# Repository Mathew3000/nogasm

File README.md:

# Warning
The pcb is not fully tested yet. Might not work as expected.

# Mods
24 LEDs on pc edge <br/>
ESP32 instead of a teensy/teensyduino<br/>
Includes KiCad files<br/>

### Case
The case can be 3D printed without support material. Print at least the top half of the case in white to see the LED display beneath. 
Files will be uploaded once tested.

### PCB
All the Gerber files are included to order a set of PCBs. The PCB has mostly surface-mount components, and is doable with either a soldering iron or solder paste.
The components have been chosen so they can be assembled by the JLCpcb Assembly service. The only part that needs to be sourced from elsewhere and handsoldered is the pressure gauge.

### Vibrator
The vibrator is made from a Mabuchi RS-555PH motor, with an eccentric mass pressed onto the shaft. These can be purchased pre-assembled, or built from the motor and some .88" to 1" diameter cylindrical brass stock.
The vibrator case is compatible with attachments designed for the Hitachi Magic Wand. The motor is press-fit or glued into the two halves of the case.

This repository is a fork of the nogasm project by headcrabned https://github.com/nogasm/nogasm 
This work is licensed under a Creative Commons Attribution-NonCommercial 4.0 International Licence, available at http://creativecommons.org/licenses/by-nc/4.0/.

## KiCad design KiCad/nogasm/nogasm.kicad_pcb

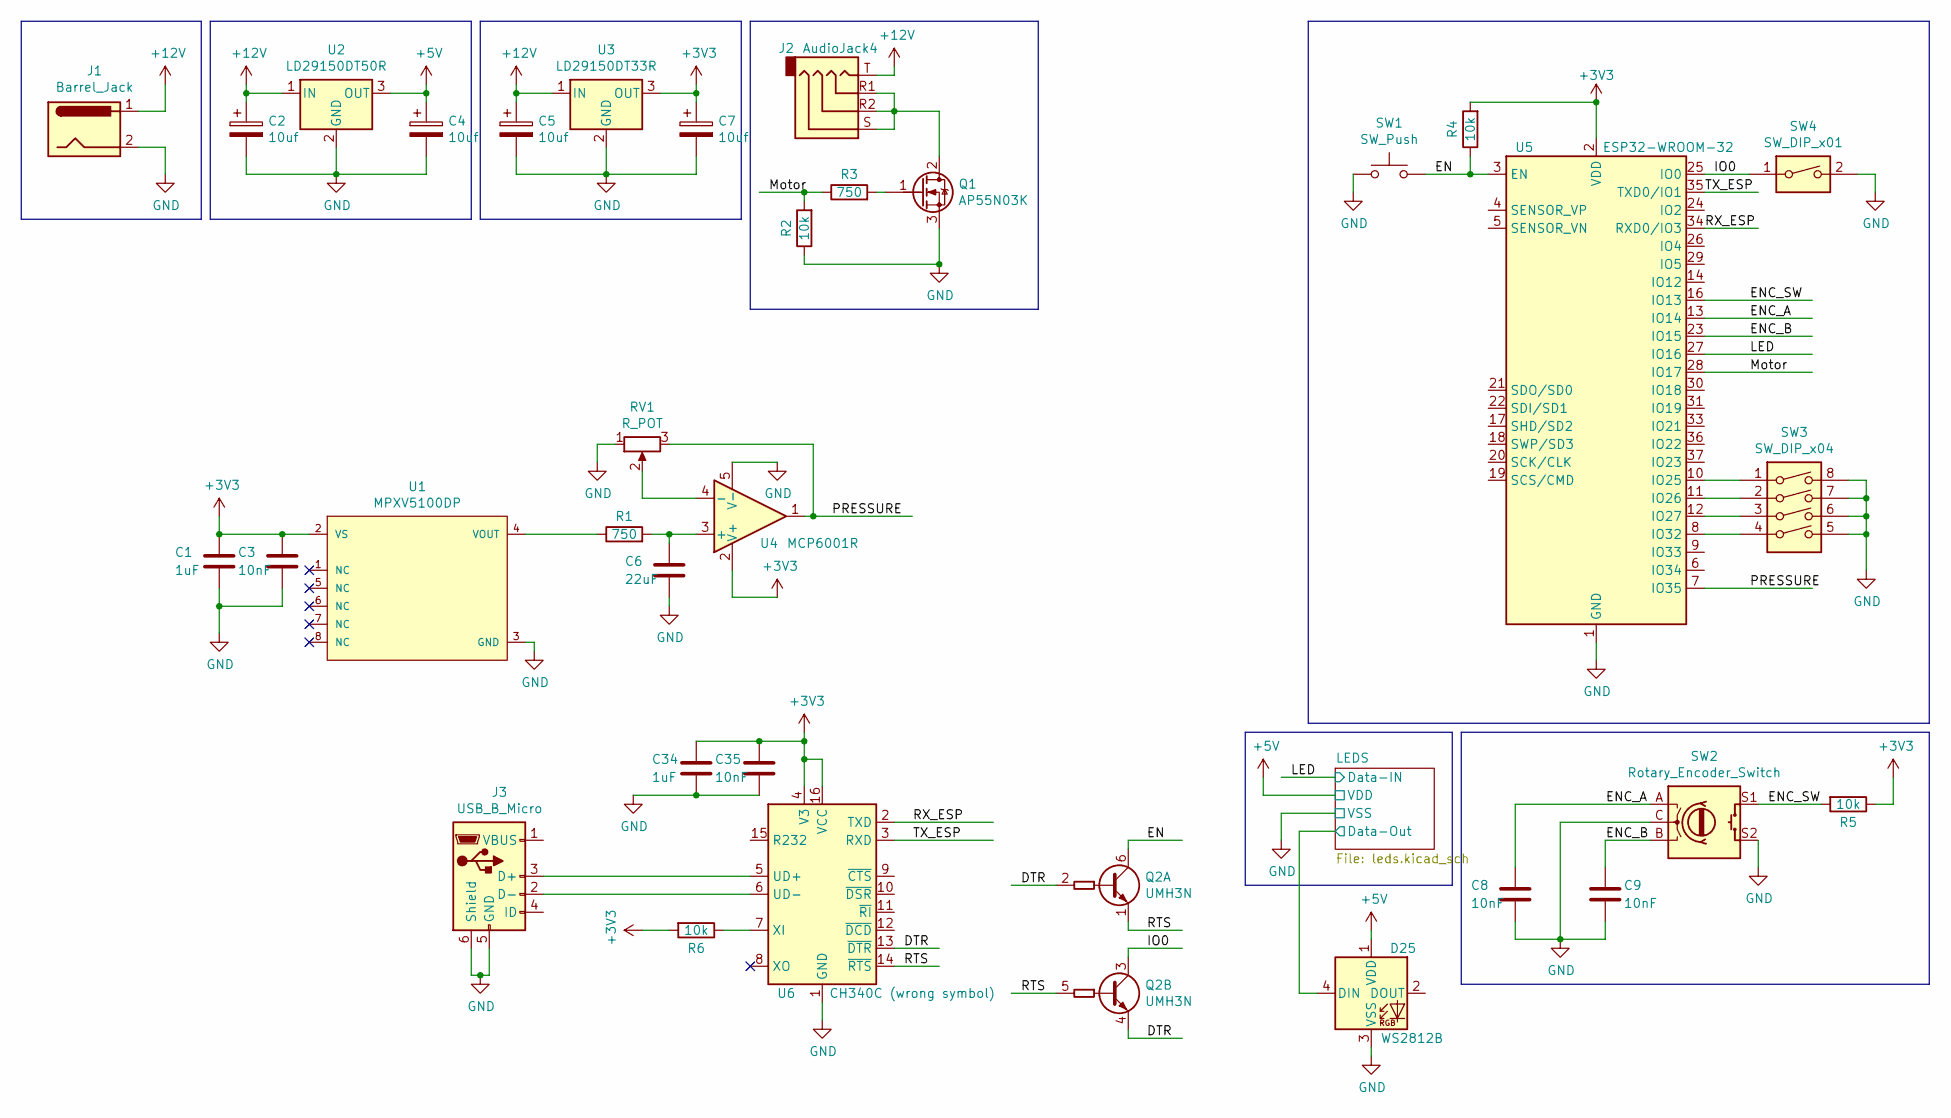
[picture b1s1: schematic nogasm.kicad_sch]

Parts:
C1, C34: 1uF; C_0603_1608Metric; LCSC C513775
C2, C4, C5, C7: 10uf; CP_Elec_4x4.5; LCSC C249787
C3, C8, C9, C35: 10nF; C_0603_1608Metric; LCSC C100042
C6: 22uF; C_1206_3216Metric; LCSC C159759
D25: WS2812B; LED_WS2812B_PLCC4_5.0x5.0mm_P3.2mm; LCSC C114586
J1: Barrel_Jack; BarrelJack_CUI_PJ-102AH_Horizontal; LCSC C718033
J2: AudioJack4; Jack_3.5mm_PJ320D_Horizontal; LCSC C521460
J3: USB_B_Micro; USB_Micro-B_Wuerth_614105150721_Vertical; LCSC C145795
Q1: AP55N03K; TO-252-2; LCSC C353074
Q2: UMH3N; SOT-363_SC-70-6; LCSC C62892
R1, R3: 750; R_0603_1608Metric; LCSC C724881
R2, R4, R5, R6: 10k; R_0603_1608Metric; LCSC C98220
RV1: R_POT; Potentiometer_Bourns_3314G_Vertical; LCSC C780220
SW1: SW_Push; SW_Push_1P1T_NO_CK_KMR2; LCSC C72443
SW2: Rotary_Encoder_Switch; RotaryEncoder_Alps_EC11E-Switch_Vertical_H20mm; LCSC C470754
SW3: SW_DIP_x04; SW_DIP_SPSTx04_Slide_6.7x11.72mm_W6.73mm_P2.54mm_LowProfile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; LCSC C54950
SW4: SW_DIP_x01; SW_DIP_SPSTx01_Slide_6.7x4.1mm_W6.73mm_P2.54mm_LowProfile_J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; LCSC C54948
U1: MPXV5100DP; Freescale_Semiconductor-SOT1693-1-03_2016-B-MFG; mouser part number 841-MPXV5100DP; digikey description PRESSURE SENSOR GAUGE DUAL 8-SOP
U2: LD29150DT50R; TO-252-2; LCSC C157411
U3: LD29150DT33R; TO-252-2; LCSC C155674
U4: MCP6001R; SOT-23-5; LCSC C154973
U5: ESP32-WROOM-32; LCSC C82899
U6: CH340C (wrong symbol); SOIC-16_3.9x9.9mm_P1.27mm; LCSC C7464026

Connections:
+3V3: C1.1, C3.1, C7.1, C34.1, C35.1, R4.2, R5.1, R6.2, U1.2 (VS), U3.3 (OUT), U4.2 (V+), U5.2 (VDD), U6.4 (V3), U6.16 (VCC)
+5V: C4.1, D25.1 (VDD), U2.3 (OUT); also elsewhere on the board
+12V: C2.1, C5.1, J1.1, J2.T, U2.1 (IN), U3.1 (IN)
/DTR: Q2.2 (B1), Q2.4 (E2), U6.13 (~DTR)
/EN: Q2.6 (C1), R4.1, SW1.2, U5.3 (EN)
/ENC_A: C8.1, SW2.A, U5.13 (IO14)
/ENC_B: C9.1, SW2.B, U5.23 (IO15)
/ENC_SW: R5.2, SW2.S1, U5.16 (IO13)
/IO0: Q2.3 (C2), SW4.1, U5.25 (IO0)
/LED: U5.27 (IO16); also elsewhere on the board
/LEDS/Data-Out: D25.4 (DIN); also elsewhere on the board
/Motor: R2.2, R3.1, U5.28 (IO17)
/PRESSURE: RV1.3, U4.1, U5.7 (IO35)
/RTS: Q2.1 (E1), Q2.5 (B2), U6.14 (~RTS)
/RX_ESP: U5.34 (RXD0/IO3), U6.2 (TXD)
/TX_ESP: U5.35 (TXD0/IO1), U6.3 (RXD)
GND: C1.2, C2.2, C3.2, C4.2, C5.2, C6.2, C7.2, C8.2, C9.2, C34.2, C35.2, D25.3 (VSS), J1.2, J3.5 (GND), J3.6 (Shield), Q1.3 (S), R2.1, RV1.1, SW1.1, SW2.C, SW2.S2, SW3.5, SW3.6, SW3.7, SW3.8, SW4.2, U1.3 (GND), U2.2 (GND), U3.2 (GND), U4.5 (V-), U5.1 (GND), U5.15 (GND), U5.38 (GND), U5.39 (GND), U6.1 (GND); also elsewhere on the board
unnamed: J3.3 (D+), U6.5 (UD+)
unnamed: J3.2 (D-), U6.6 (UD-)
unnamed: J2.R1, J2.R2, J2.S, Q1.2 (D)
unnamed: Q1.1 (G), R3.2
unnamed: R1.1, U1.4 (VOUT)
unnamed: C6.1, R1.2, U4.3 (+)
unnamed: RV1.2, U4.4 (-)
unnamed: SW3.1, U5.10 (IO25)
unnamed: SW3.2, U5.11 (IO26)
unnamed: SW3.3, U5.12 (IO27)
unnamed: SW3.4, U5.8 (IO32)
unnamed: R6.1, U6.7 (XI)

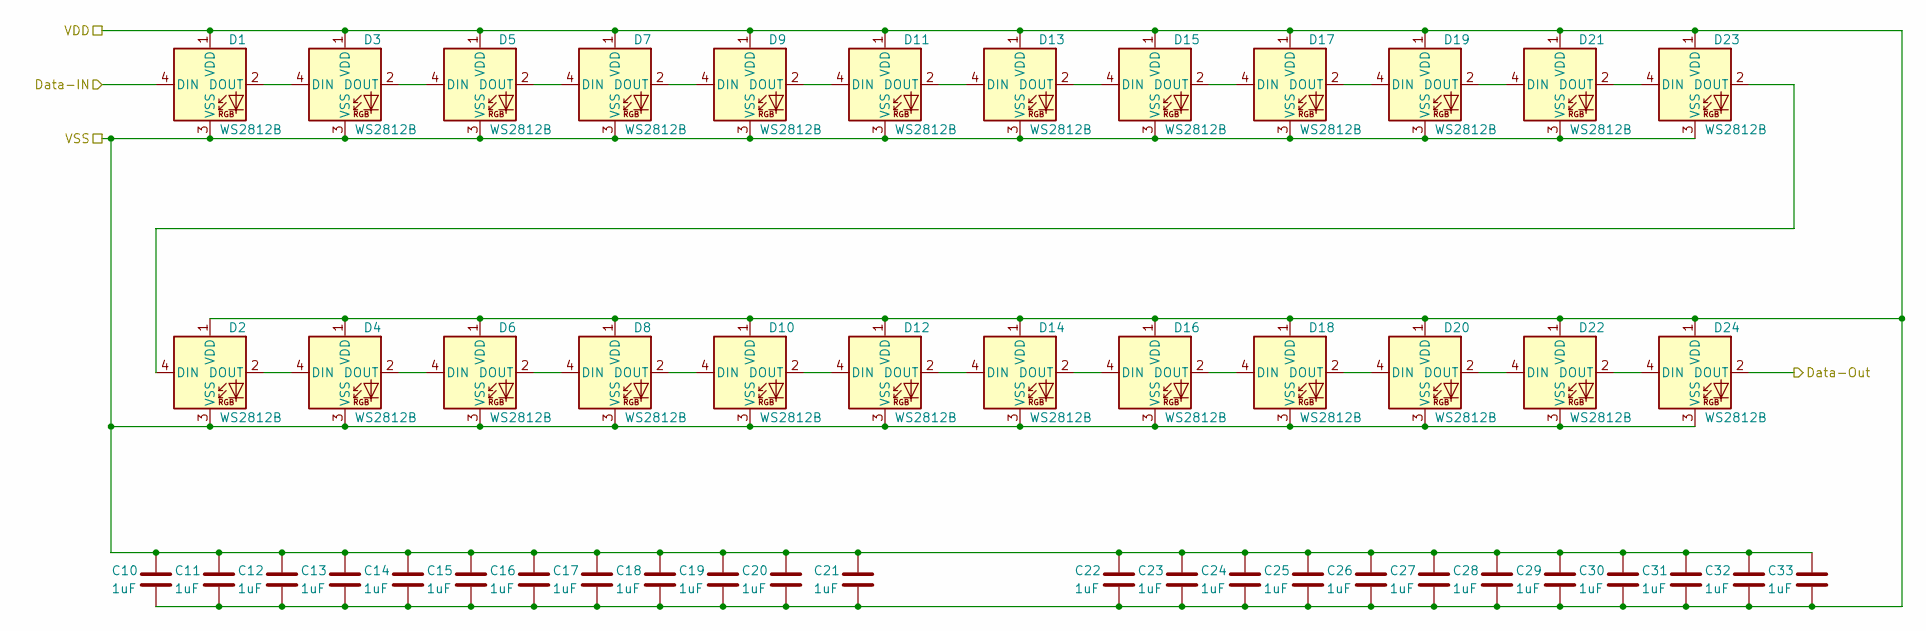
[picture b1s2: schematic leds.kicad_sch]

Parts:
C10, C11, C12, C13, C14, C15, C16, C17, C18, C19, C20, C21, C22, C23, C24, C25, C26, C27, C28, C29, C30, C31, C32, C33: 1uF; C_0603_1608Metric; LCSC C513775
D1, D2, D3, D4, D5, D6, D7, D8, D9, D10, D11, D12, D13, D14, D15, D16, D17, D18, D19, D20, D21, D22, D23, D24: WS2812B; LED_WS2812B_PLCC4_5.0x5.0mm_P3.2mm; LCSC C114586

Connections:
+5V: C10.2, C11.2, C12.2, C13.2, C14.2, C15.2, C16.2, C17.2, C18.2, C19.2, C20.2, C21.2, C22.2, C23.2, C24.2, C25.2, C26.2, C27.2, C28.2, C29.2, C30.2, C31.2, C32.2, C33.2, D1.1 (VDD), D2.1 (VDD), D3.1 (VDD), D4.1 (VDD), D5.1 (VDD), D6.1 (VDD), D7.1 (VDD), D8.1 (VDD), D9.1 (VDD), D10.1 (VDD), D11.1 (VDD), D12.1 (VDD), D13.1 (VDD), D14.1 (VDD), D15.1 (VDD), D16.1 (VDD), D17.1 (VDD), D18.1 (VDD), D19.1 (VDD), D20.1 (VDD), D21.1 (VDD), D22.1 (VDD), D23.1 (VDD), D24.1 (VDD); also elsewhere on the board
/LED: D1.4 (DIN); also elsewhere on the board
/LEDS/Data-Out: D24.2 (DOUT); also elsewhere on the board
GND: C10.1, C11.1, C12.1, C13.1, C14.1, C15.1, C16.1, C17.1, C18.1, C19.1, C20.1, C21.1, C22.1, C23.1, C24.1, C25.1, C26.1, C27.1, C28.1, C29.1, C30.1, C31.1, C32.1, C33.1, D1.3 (VSS), D2.3 (VSS), D3.3 (VSS), D4.3 (VSS), D5.3 (VSS), D6.3 (VSS), D7.3 (VSS), D8.3 (VSS), D9.3 (VSS), D10.3 (VSS), D11.3 (VSS), D12.3 (VSS), D13.3 (VSS), D14.3 (VSS), D15.3 (VSS), D16.3 (VSS), D17.3 (VSS), D18.3 (VSS), D19.3 (VSS), D20.3 (VSS), D21.3 (VSS), D22.3 (VSS), D23.3 (VSS), D24.3 (VSS); also elsewhere on the board
unnamed: D1.2 (DOUT), D3.4 (DIN)
unnamed: D2.4 (DIN), D23.2 (DOUT)
unnamed: D2.2 (DOUT), D4.4 (DIN)
unnamed: D3.2 (DOUT), D5.4 (DIN)
unnamed: D4.2 (DOUT), D6.4 (DIN)
unnamed: D5.2 (DOUT), D7.4 (DIN)
unnamed: D6.2 (DOUT), D8.4 (DIN)
unnamed: D7.2 (DOUT), D9.4 (DIN)
unnamed: D8.2 (DOUT), D10.4 (DIN)
unnamed: D10.2 (DOUT), D12.4 (DIN)
unnamed: D9.2 (DOUT), D11.4 (DIN)
unnamed: D11.2 (DOUT), D13.4 (DIN)
unnamed: D12.2 (DOUT), D14.4 (DIN)
unnamed: D13.2 (DOUT), D15.4 (DIN)
unnamed: D14.2 (DOUT), D16.4 (DIN)
unnamed: D15.2 (DOUT), D17.4 (DIN)
unnamed: D16.2 (DOUT), D18.4 (DIN)
unnamed: D17.2 (DOUT), D19.4 (DIN)
unnamed: D18.2 (DOUT), D20.4 (DIN)
unnamed: D19.2 (DOUT), D21.4 (DIN)
unnamed: D20.2 (DOUT), D22.4 (DIN)
unnamed: D21.2 (DOUT), D23.4 (DIN)
unnamed: D22.2 (DOUT), D24.4 (DIN)

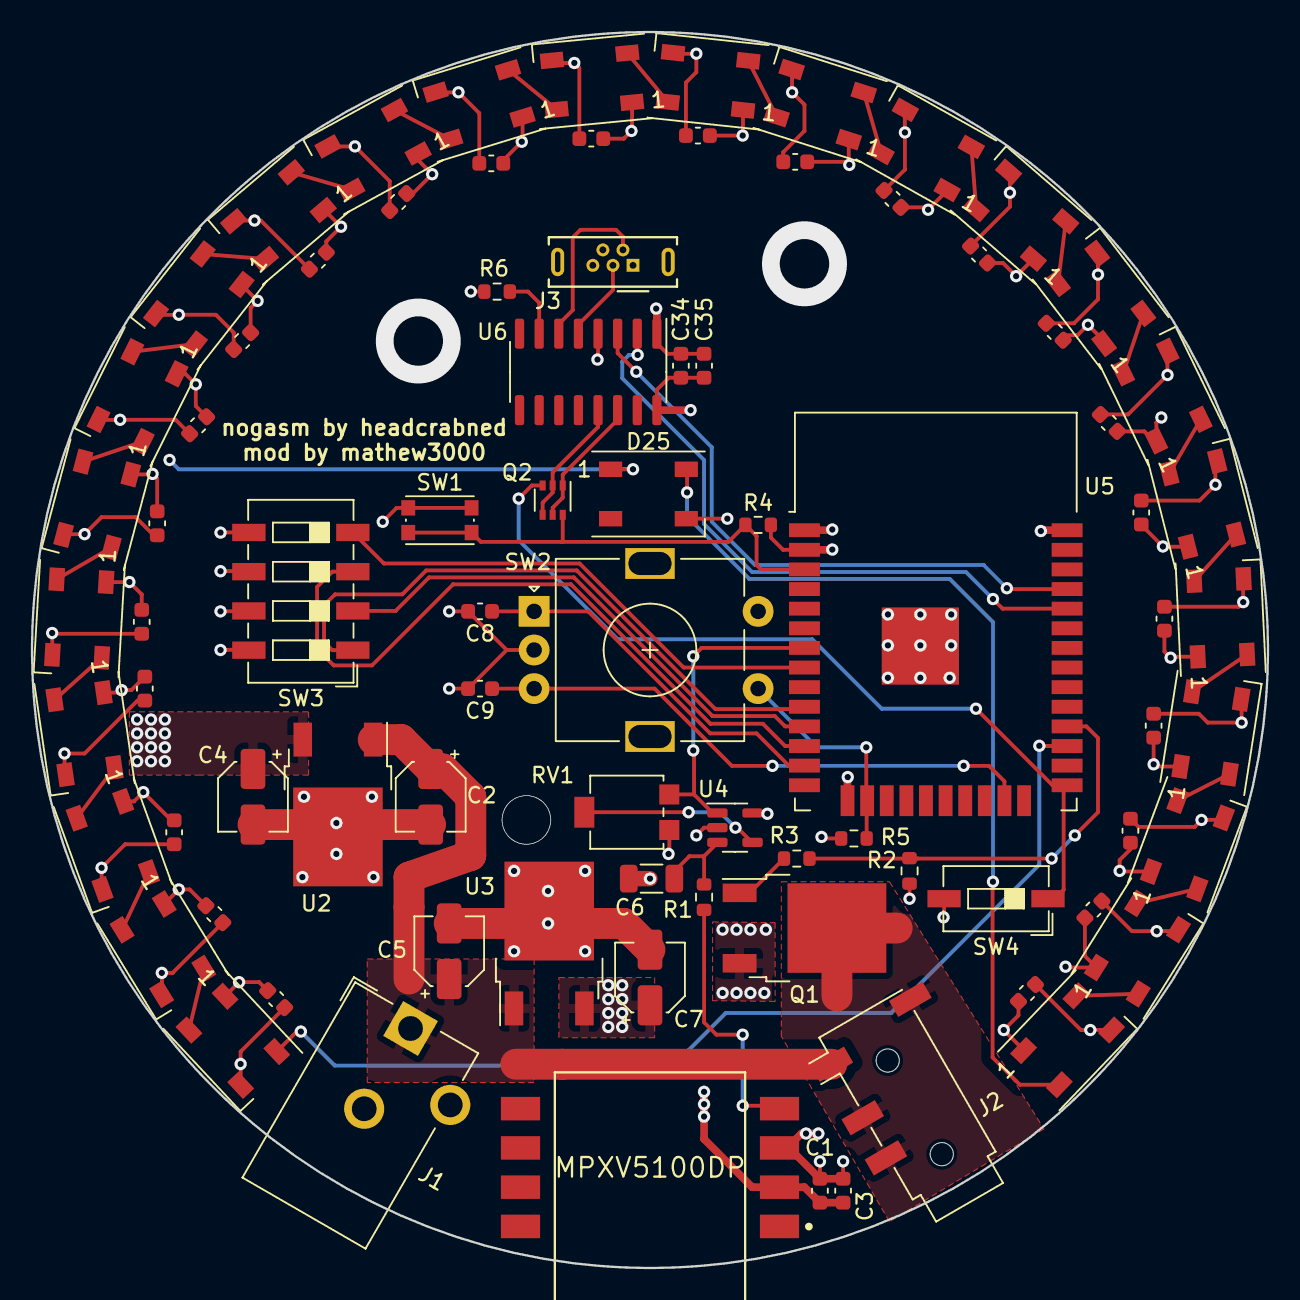
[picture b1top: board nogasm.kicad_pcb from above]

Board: 4 copper layers, 80.0 x 80.0 mm, 82 parts (0 on the bottom side), 52 nets.

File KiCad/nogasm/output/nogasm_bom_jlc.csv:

"Comment","Designator","Footprint","LCSC Part #"
"1uF","C1,C34,C10,C11,C12,C13,C14,C15,C16,C17,C18,C19,C20,C21,C23,C22,C24,C25,C26,C27,C28,C29,C30,C31,C32,C33","C_0603_1608Metric","C513775"
"10uf","C2,C4,C5,C7","CP_Elec_4x4.5","C249787"
"33uF","C6","C_1206_3216Metric","C342633"
"10nF","C8,C9,C3,C35","C_0603_1608Metric","C100042"
"WS2812B","D1,D3,D5,D7,D9,D11,D13,D15,D17,D19,D23,D24,D22,D20,D18,D16,D14,D12,D10,D8,D6,D4,D2,D21","LED_WS2812B_PLCC4_5.0x5.0mm_P3.2mm","C114586"
"Barrel_Jack","J1","BarrelJack_CUI_PJ-102AH_Horizontal","C718033"
"AudioJack4","J2","Jack_3.5mm_PJ320D_Horizontal","C521460"
"USB_B_Micro","J3","USB_Micro-B_Wuerth_614105150721_Vertical","C145795"
"AP55N03K","Q1","TO-252-2","C353074"
"750","R1,R3","R_0603_1608Metric","C724881"
"10k","R4,R5,R2,R6","R_0603_1608Metric","C98220"
"R_POT","RV1","Potentiometer_Bourns_3314G_Vertical","C780220"
"SW_Push","SW1","SW_Push_1P1T_NO_CK_KMR2","C72443"
"Rotary_Encoder_Switch","SW2","RotaryEncoder_Alps_EC11E-Switch_Vertical_H20mm","C470754"
"SW_DIP_x04","SW3","SW_DIP_SPSTx04_Slide_6.7x11.72mm_W6.73mm_P2.54mm_LowProfile_JPin","C54950"
"SW_DIP_x01","SW4","SW_DIP_SPSTx01_Slide_6.7x4.1mm_W6.73mm_P2.54mm_LowProfile_JPin","C54948"
"LD29150DT50R","U2","TO-252-2","C157411"
"BL1117-33CY","U3","TO-252-2","C165080"
"MCP6001R","U4","SOT-23-5","C154973"
"ESP32-WROOM-32","U5","ESP32-WROOM-32","C82899"
"CH340B (wrong symbol)","U6","SOIC-16_3.9x9.9mm_P1.27mm","C81010"

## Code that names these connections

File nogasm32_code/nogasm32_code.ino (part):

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 * other than the default 15 seconds, and options for LED brightness and enabling/
 * disabling beeps. Four DIP switches are included on the board to allow users to
 * change other software settings without reflashing code. One example use would 
 * be switch 1 toggling between the defaul ramping motor behavior, and a strict
 * ON/OFF output to the motor that could instead be used to toggle a relay for 
 * driving other toys.
 * 
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#define BRIGHTNESS 255

//Encoder
#define ENC_SW   13 //Pushbutton on the encoder
ESP32Encoder myEnc;

//DIP Switches
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bool SW2 =        false;
bool SW3 =        false;
bool SW4 =        false;
#define MOT_MIN 20  // Motor PWM minimum.  It needs a little more than this to start.

CRGB leds[NUM_LEDS];

int pressure = 0;
int avgPressure = 0; //Running 25 second average pressure
//int bri =100; //Brightness setting
int rampTimeS = 30; //Ramp-up time, in seconds
#define DEFAULT_PLIMIT 600
int pLimit = DEFAULT_PLIMIT; //Limit in change of pressure before the vibrator turns off
int maxSpeed = 255; //maximum speed the motor will ramp up to in automatic mode
float motSpeed = 0; //Motor speed, 0-255 (float to maintain smooth ramping to low speeds)

//=======EEPROM Addresses============================
//128b available on teensy LC
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    FastLED.show();
  }

  pinMode(ENC_SW,   INPUT); //Pin to read quadrature pulses from encoder

  myEnc.attachHalfQuad(15, 14); //encoder inputs on pins 14,15

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  
  raPressure.clear(); //Initialize a running pressure average

  digitalWrite(MOTPIN, LOW);//Make sure the motor is off
  ledcSetup(MOT_CHAN, 500, 8);
  ledcAttachPin(MOTPIN, MOT_CHAN);

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  ledcWrite(MOT_CHAN, motSpeed);

  //gyrGraphDraw(avgPressure, 0, 4 * 3 * NUM_LEDS);
  int presDraw = map(constrain(pressure - avgPressure, 0, pLimit),0,pLimit,0,NUM_LEDS*3);
  draw_bars_3(presDraw, CRGB::Green,CRGB::Yellow,CRGB::Red);
  draw_cursor(knob, CRGB::Red);
}
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    ledcWrite(MOT_CHAN, 0);
  }

  int presDraw = map(constrain(pressure - avgPressure, 0, pLimit),0,pLimit,0,NUM_LEDS*3);
  draw_bars_3(presDraw, CRGB::Green,CRGB::Yellow,CRGB::Red);
  draw_cursor_3(knob, CRGB(50,50,200),CRGB::Blue,CRGB::Purple);

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    switch(state){
      case MANUAL:
        myEnc.setCount(sensitivity);//Whenever going into auto mode, keep the last sensitivity
        motSpeed = 0; //Also reset the motor speed to 0
        return AUTO;
      case AUTO:
        myEnc.setCount(0);//Whenever going into manual mode, set the speed to 0.
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        avgPressure = raPressure.getAverage();
      }
      
      pressure = analogRead(BUTTPIN);
      fadeToBlackBy(leds,NUM_LEDS,20); //Create a fading light effect. LED buffer is not otherwise cleared
      uint8_t btnState = check_button();
      state = set_state(btnState,state); //Set the next state based on this state and button presses
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
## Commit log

2021-08-08 Added ESP-32 Based PCB project
2021-08-08 Added Modifications to Readme
2021-08-08 Added text and mounting holes
2021-08-26 Added ESP32-Based KiCad files
2021-08-26 Added warning to readme
2021-08-26 Moved kicad outputs to pcb folder
2021-08-26 Corrected partnumber for 3v3 LDO
2021-08-26 Fixed BOM to include correct 3v3 LDO
2021-08-26 modified readme to explain project changes
2021-08-26 Removed all STL files and incompatible code.
2021-08-26 Added code for nogasm32 pressure logger
2021-08-26 added Telnet base
2021-08-26 Fixed Telnet code
2021-08-26 Changed Pressurelogger to use non ADC2 pin
2021-08-26 Added basic code conversion
2021-08-26 Updated PCB documents to fix ESP ADC channel
2021-08-26 Updated PCB Files
2021-08-26 Added hostname to esp wifi
2021-08-26 Added first working ported code
2021-08-27 Added Autoflash for ESP32 and Center-LED
2021-08-27 Added new Fabrication outputs
2021-08-27 Annotated Schematic files
2021-09-02 Added untested case stl
2022-08-14 Updated to new KicadFormat
2022-08-14 added Logger and plotter
2022-08-25 Updated pcb layout and 3d model
2022-08-25 Added output folder to gitignore
2023-01-13 fixed missing ground and vcc for 2 leds because of esp keepout
2023-03-01 added 3D files for case
2024-05-02 updated parts for jlc
2024-12-10 updated pindefinitions to match kicad
